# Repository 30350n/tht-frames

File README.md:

# THT-Frames

THT-Frames is a through hole version of [Mutable Instruments Frames](https://mutable-instruments.net/modules/frames/).
For the MCU a **128KB** STM32F103C8T6/STM32F103CBT6 "bluepill type" module is used.
**Warning! Most of the conventional boards floating around on ebay, aliexpress, etc. are 64KB. Those won't work with the provided firmware.**
I'd recommend picking one up from robotdyn ([website](https://robotdyn.com/)/[aliexpress](https://robotdyn.aliexpress.com/store/1950989)), these are the ones I use and they work without any problems.
You can also pickup a matching APM32 board if you want for a little cheaper. I've tested them and they also seem to work fine.

It also uses a different dac than the original, because it isn't available as a DIP package.

## Panels

Be sure to check out my [printable-instruments](https://github.com/30350n/printable-instruments) repository, which contains pcb panels for several Mutable Instuments modules including Frames.
That being said, any third-party panels should also fit with these boards.

## How to use

### Quickstart

To get started quickly, you can just download the gerbers for both pcbs and the compiled software `.hex` file from the [Releases](https://github.com/30350n/tht-frames/releases) section.

### Hardware

If you want to export the gerbers yourself or modify them, just clone the repository and open the hardware files with KiCad.

### Software

This project requires slightly modified software, because it uses two 2-channel DACs instead of the single 4-channel DAC the original uses.

If you want to build the software yourself, clone the [mutable-dev-environment](https://github.com/pichenettes/mutable-dev-environment) repository and follow the provided instructions to set it up.
After that, copy the patch from this repository (`software/tht-frames.patch`) to `mutable-dev-environment/eurorack-modules` and also `cd` to that directory.
Finally apply the patch via `git apply tht-frames.patch` and build the firmware as usual.

## Credits
- **[Mutable Instruments](https://github.com/pichenettes/eurorack)** provided the original hardware design files and software which this projects builds upon.
- **[SoundForce - Braids Through-hole](http://sound-force.nl/?page_id=3179)** gave me the idea for this project.

## License
- Hardware: cc-by-sa-3.0
- Software: MIT

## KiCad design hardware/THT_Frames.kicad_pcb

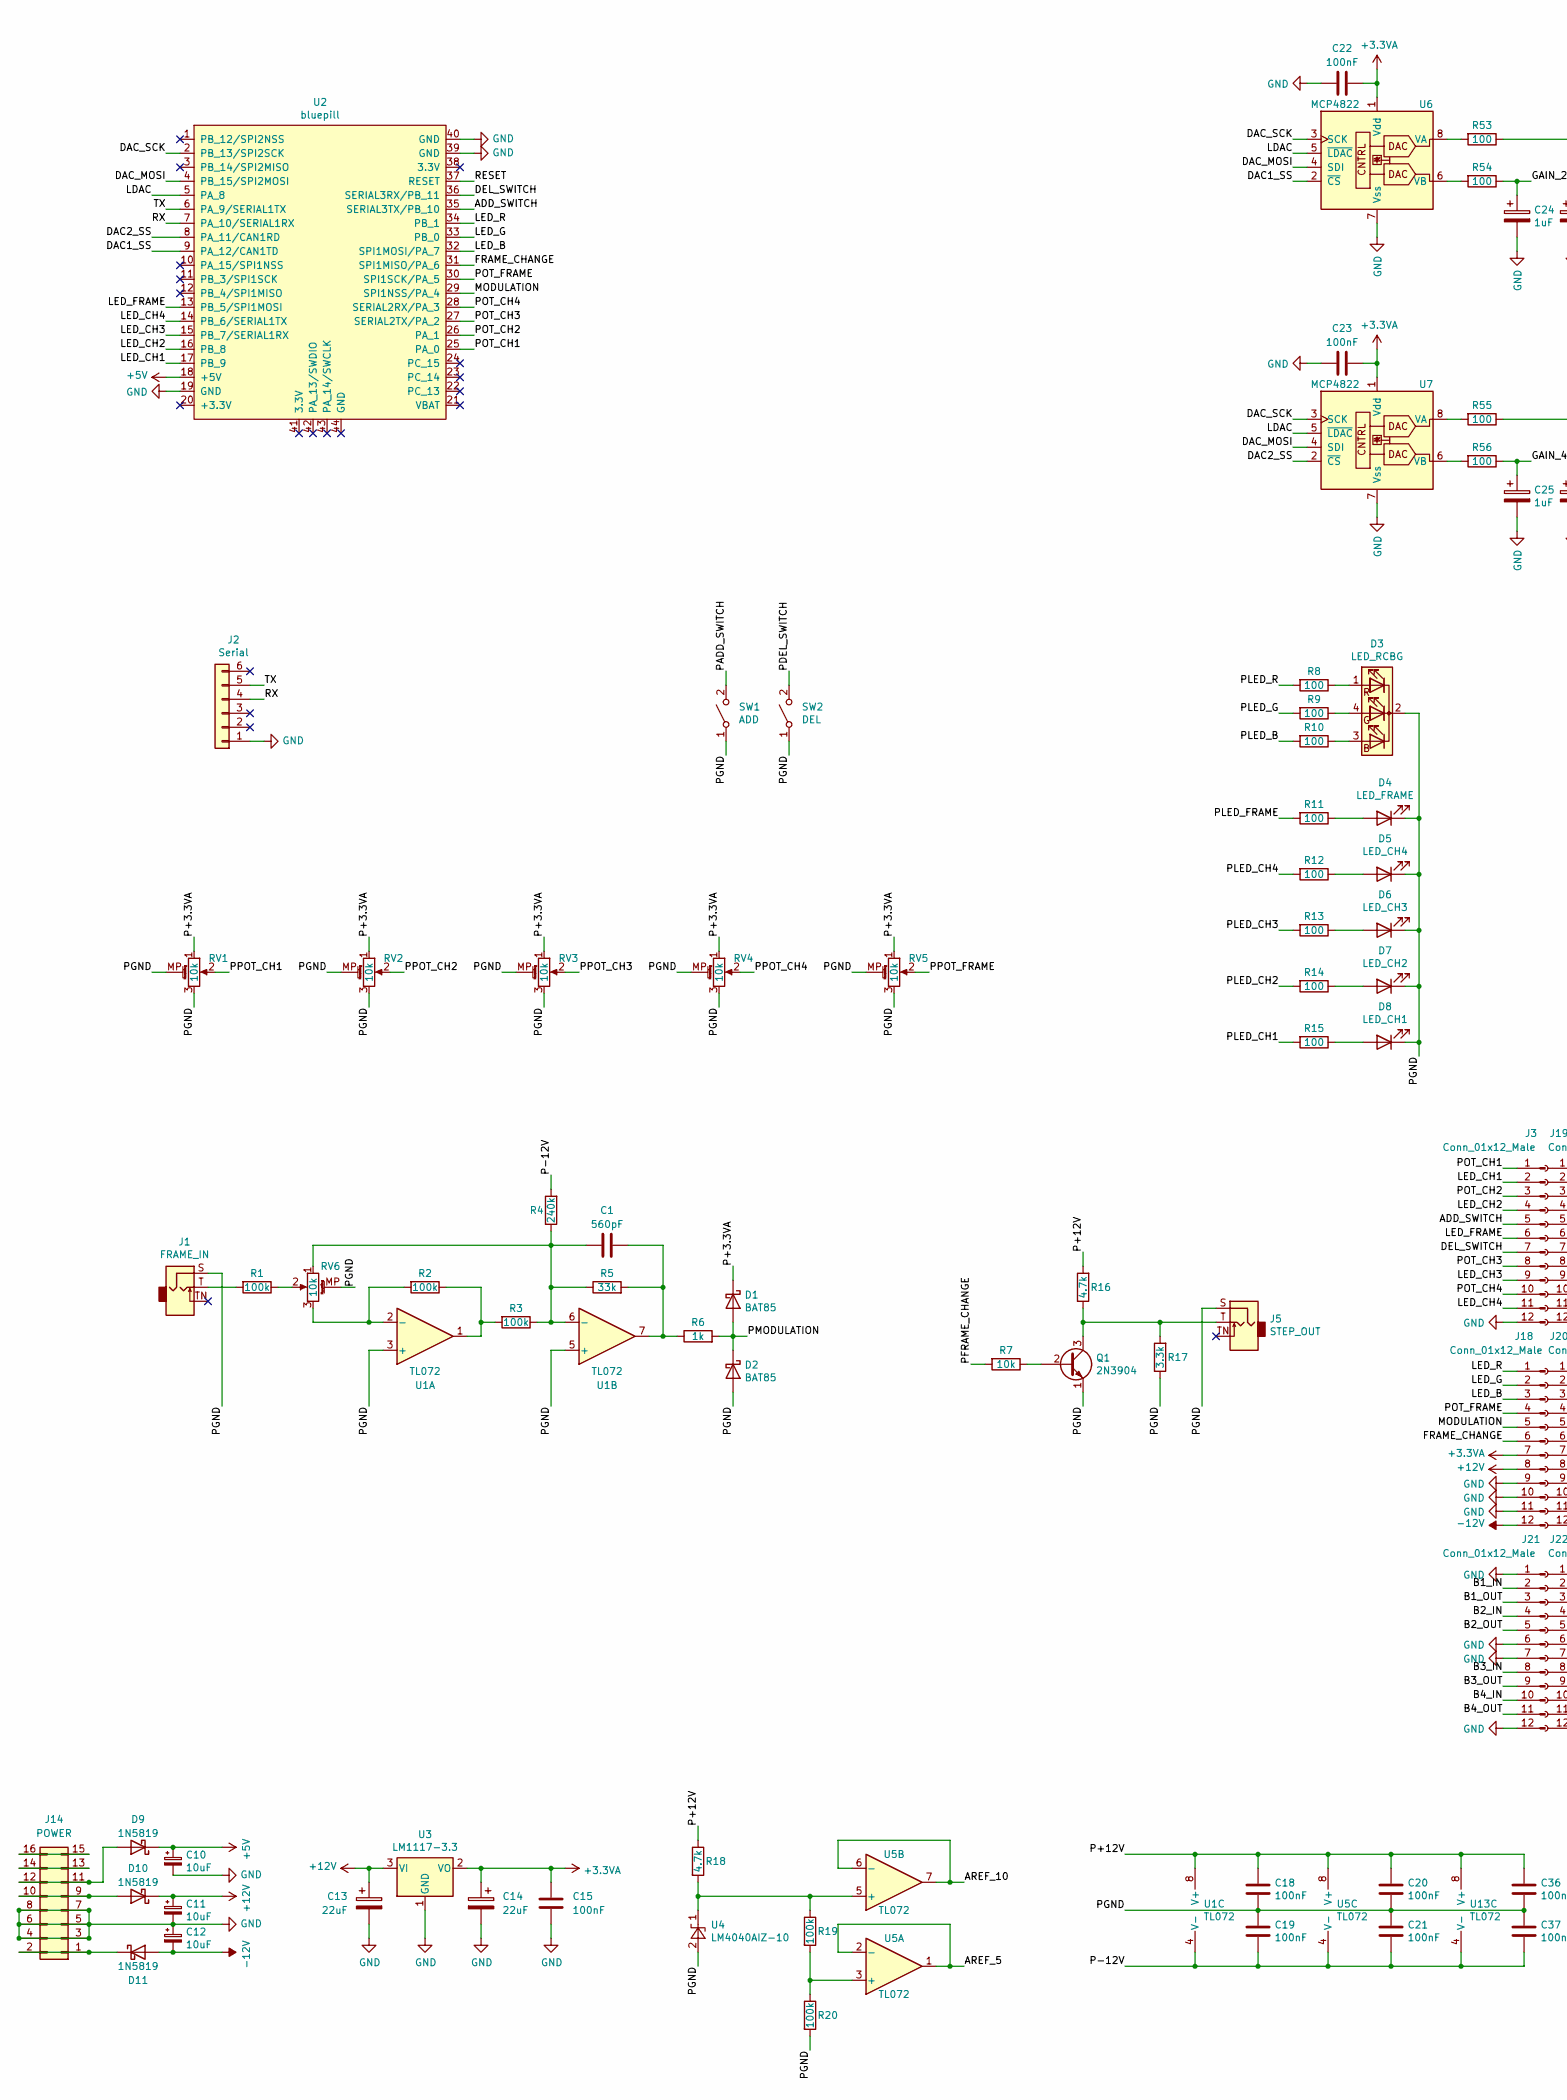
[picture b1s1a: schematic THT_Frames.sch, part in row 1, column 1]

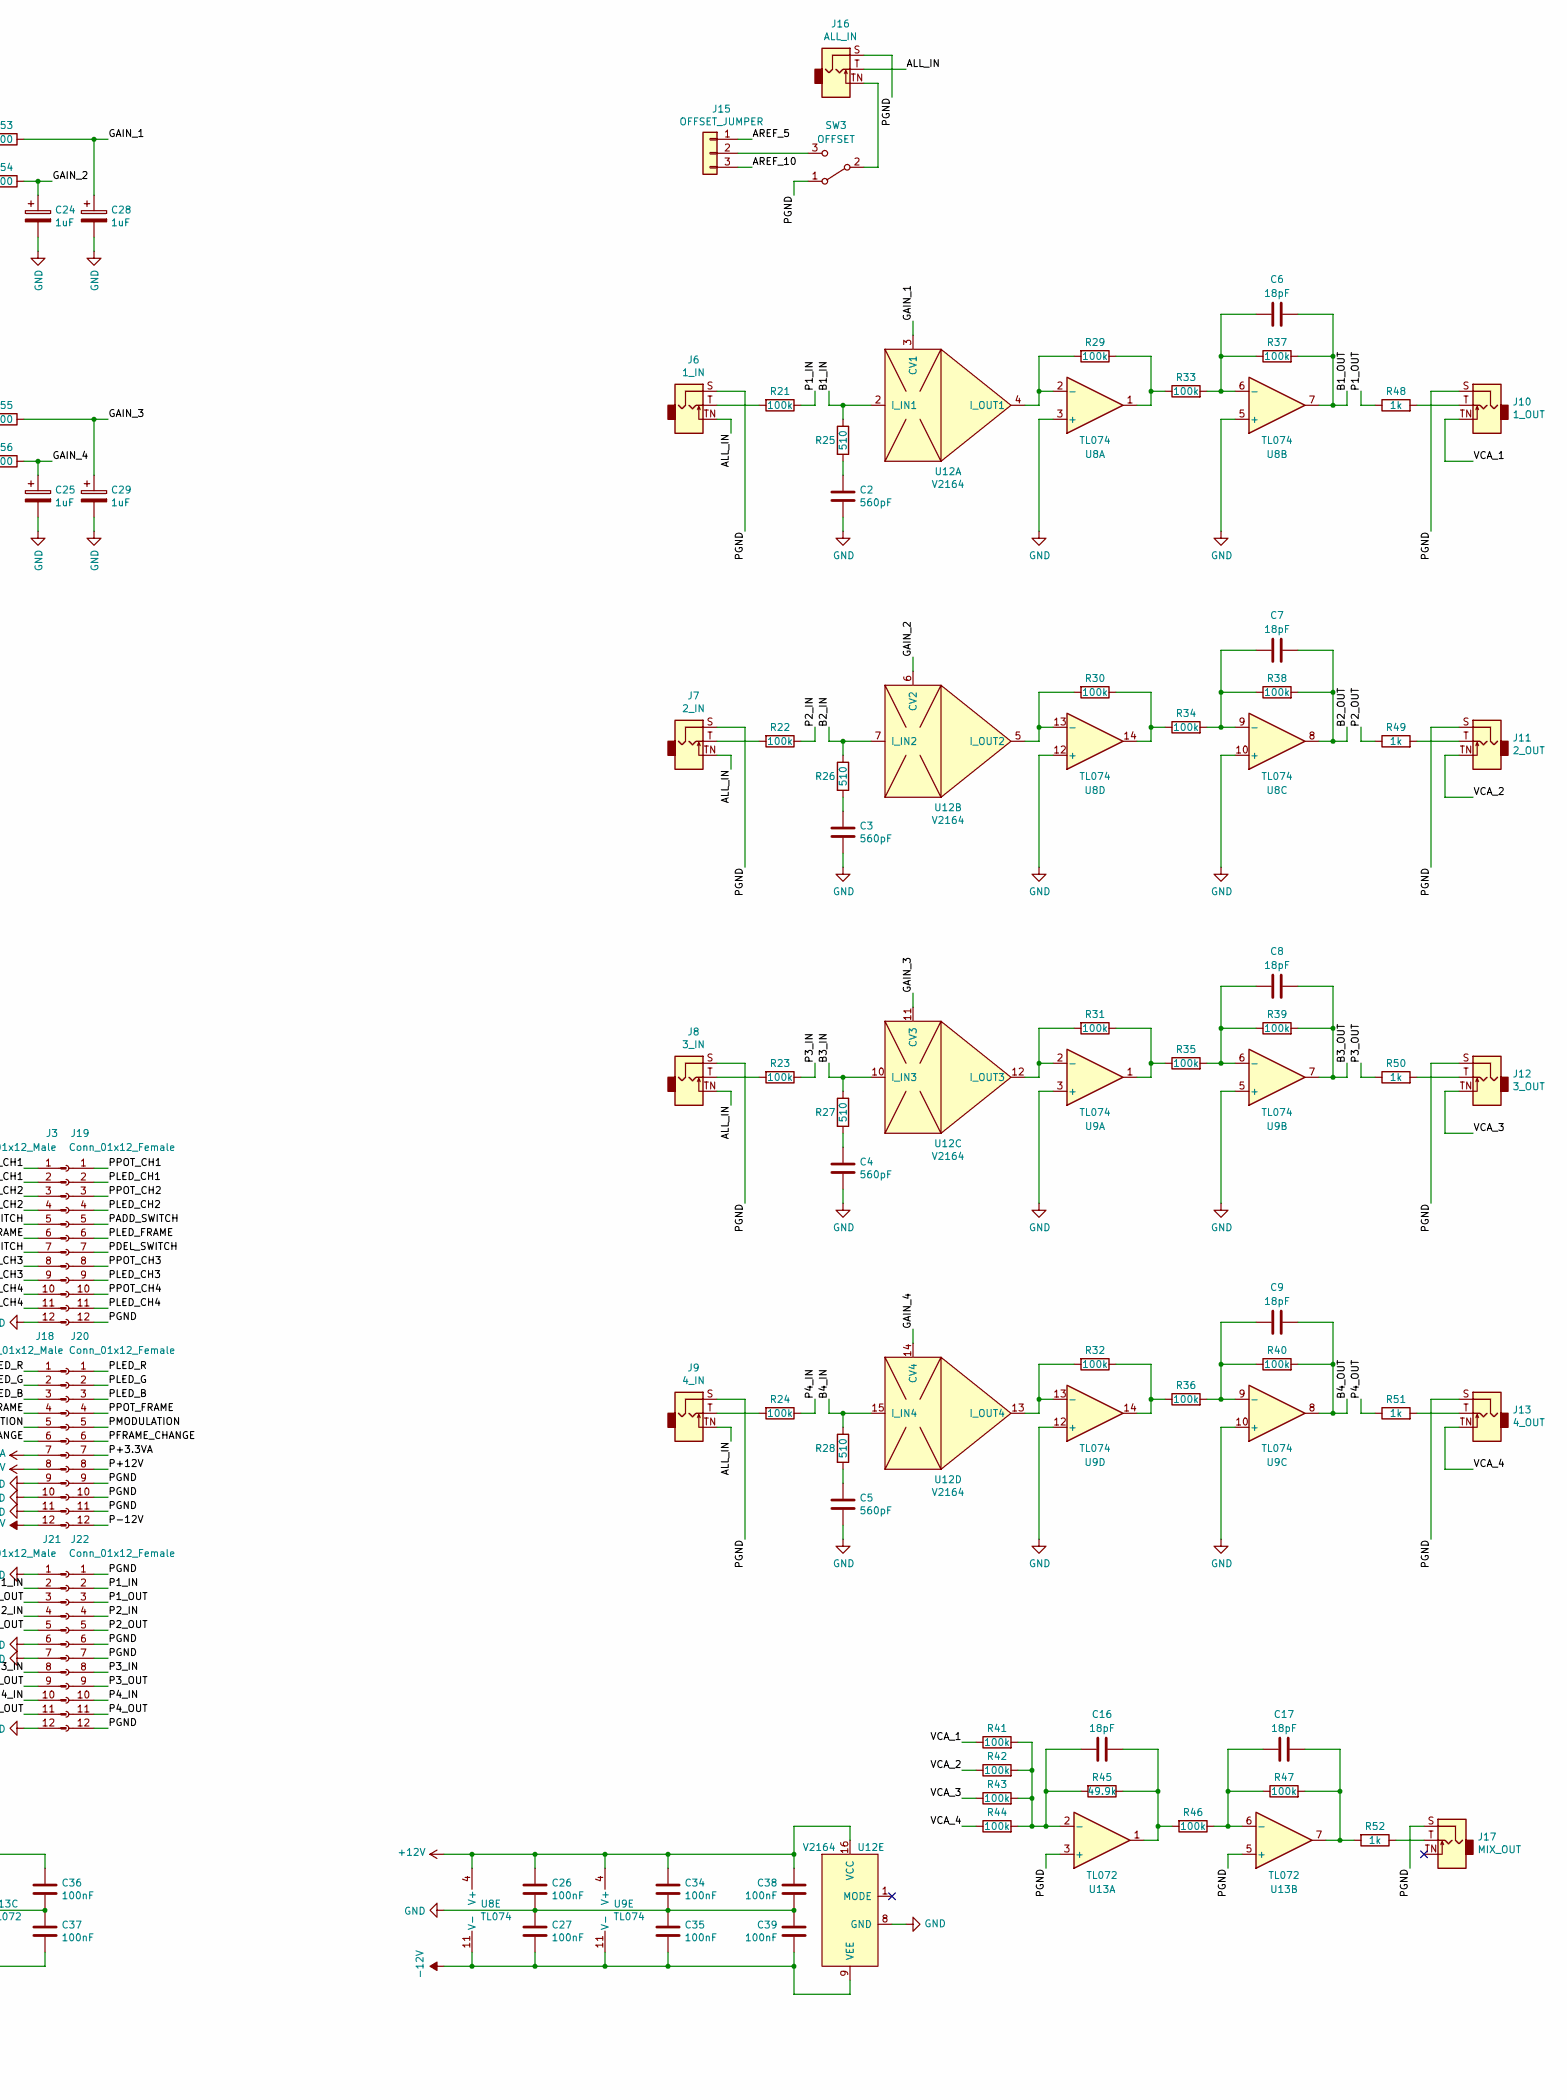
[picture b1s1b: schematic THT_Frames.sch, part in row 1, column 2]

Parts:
C1, C2, C3, C4, C5: 560pF; C_Disc_D5.0mm_W2.5mm_P5.00mm_silk
C6, C7, C8, C9, C16, C17: 18pF; C_Disc_D5.0mm_W2.5mm_P5.00mm_silk
C10, C11, C12: 10uF; CP_Radial_D5.0mm_P2.00mm_silk
C13, C14: 22uF; CP_Radial_D5.0mm_P2.00mm_silk
C15, C18, C19, C20, C21, C22, C23, C26, C27, C34, C35, C36, C37, C38, C39: 100nF; C_Disc_D5.0mm_W2.5mm_P5.00mm_silk
C24, C25, C28, C29: 1uF; C_Disc_D7.5mm_W5.0mm_P5.00mm_silk
D1, D2: BAT85; D_DO-41_SOD81_P7.62mm_Horizontal_silk
D3: LED_RCBG; LED_D5.0mm-4_RGB
D4: LED_FRAME; LED_D5.0mm
D5: LED_CH4; LED_D3.0mm
D6: LED_CH3; LED_D3.0mm
D7: LED_CH2; LED_D3.0mm
D8: LED_CH1; LED_D3.0mm
D9, D10, D11: 1N5819; D_DO-41_SOD81_P10.16mm_Horizontal_silk
J1: FRAME_IN; Jack_3.5mm_QingPu_WQP-PJ398SM_Vertical_CircularHoles_better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
J2: Serial; PinHeader_1x06_P2.54mm_Vertical
J3, J18, J21: Conn_01x12_Male; PinHeader_1x12_P2.54mm_Vertical
J5: STEP_OUT; Jack_3.5mm_QingPu_WQP-PJ398SM_Vertical_CircularHoles_better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
J6: 1_IN; Jack_3.5mm_QingPu_WQP-PJ398SM_Vertical_CircularHoles_better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
J7: 2_IN; Jack_3.5mm_QingPu_WQP-PJ398SM_Vertical_CircularHoles_better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
J8: 3_IN; Jack_3.5mm_QingPu_WQP-PJ398SM_Vertical_CircularHoles_better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
J9: 4_IN; Jack_3.5mm_QingPu_WQP-PJ398SM_Vertical_CircularHoles_better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
J10: 1_OUT; Jack_3.5mm_QingPu_WQP-PJ398SM_Vertical_CircularHoles_better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
J11: 2_OUT; Jack_3.5mm_QingPu_WQP-PJ398SM_Vertical_CircularHoles_better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
J12: 3_OUT; Jack_3.5mm_QingPu_WQP-PJ398SM_Vertical_CircularHoles_better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
J13: 4_OUT; Jack_3.5mm_QingPu_WQP-PJ398SM_Vertical_CircularHoles_better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
J14: POWER; IDC-Header_2x08_P2.54mm_Vertical_eurorack
J15: OFFSET_JUMPER; PinHeader_1x03_P2.54mm_Vertical
J16: ALL_IN; Jack_3.5mm_QingPu_WQP-PJ398SM_Vertical_CircularHoles_better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
J17: MIX_OUT; Jack_3.5mm_QingPu_WQP-PJ398SM_Vertical_CircularHoles_better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
J19, J20, J22: Conn_01x12_Female; PinSocket_1x12_P2.54mm_Vertical
Q1: 2N3904; TO-92_Inline_Wide_silk
R1, R2, R3, R19, R20, R21, R22, R23, R24, R29, R30, R31, R32, R33, R34, R35, R36, R37, R38, R39, R40, R41, R42, R43, R44, R46, R47: 100k; R_Axial_DIN0207_L6.3mm_D2.5mm_P7.62mm_Horizontal_silk
R4: 240k; R_Axial_DIN0207_L6.3mm_D2.5mm_P7.62mm_Horizontal_silk
R5: 33k; R_Axial_DIN0207_L6.3mm_D2.5mm_P7.62mm_Horizontal_silk
R6, R48, R49, R50, R51, R52: 1k; R_Axial_DIN0207_L6.3mm_D2.5mm_P7.62mm_Horizontal_silk
R7: 10k; R_Axial_DIN0207_L6.3mm_D2.5mm_P7.62mm_Horizontal_silk
R8, R9, R10, R11, R12, R13, R14, R15, R53, R54, R55, R56: 100; R_Axial_DIN0207_L6.3mm_D2.5mm_P7.62mm_Horizontal_silk
R16, R18: 4.7k; R_Axial_DIN0207_L6.3mm_D2.5mm_P7.62mm_Horizontal_silk
R17: 3.3k; R_Axial_DIN0207_L6.3mm_D2.5mm_P7.62mm_Horizontal_silk
R25, R26, R27, R28: 510; R_Axial_DIN0207_L6.3mm_D2.5mm_P7.62mm_Horizontal_silk
R45: 49.9k; R_Axial_DIN0207_L6.3mm_D2.5mm_P7.62mm_Horizontal_silk
RV1, RV2, RV3, RV4, RV5, RV6: 10k; Potentiometer_Alps_RK09K_Single_Vertical_better_origin
SW1: ADD; Push_E-Switch_KS01Q01_silk_better_origin
SW2: DEL; Push_E-Switch_KS01Q01_silk_better_origin
SW3: OFFSET; sw_spdt_slide_CS12ANW03
U1, U5, U13: TL072; DIP-8_W7.62mm_Socket_LongPads_silk
U2: bluepill
U3: LM1117-3.3; TO-220-3_Horizontal_TabDown_silk
U4: LM4040AIZ-10; TO-92_Inline_Wide_silk
U6, U7: MCP4822; DIP-8_W7.62mm_Socket_LongPads_silk
U8, U9: TL074; DIP-14_W7.62mm_Socket_LongPads_silk
U12: V2164; DIP-16_W7.62mm_Socket_LongPads_silk

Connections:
+3.3VA: C14.1, C15.1, C22.1, C23.1, J18.7, U3.2 (VO), U6.1 (Vdd), U7.1 (Vdd)
+5V: C10.1, D9.1 (K), U2.18 (+5V)
+12V: C11.1, C13.1, C26.1, C34.1, C38.1, D10.1 (K), J18.8, U3.3 (VI), U8.4 (V+), U9.4 (V+), U12.16 (VCC)
-12V: C12.2, C27.2, C35.2, C39.2, D11.2 (A), J18.12, U8.11 (V-), U9.11 (V-), U12.9 (VEE)
/ADD_SWITCH: J3.5, U2.35 (SERIAL3TX/PB_10)
/ALL_IN: J6.TN, J7.TN, J8.TN, J9.TN, J16.T
/AREF_5: J15.1, U5.1, U5.2 (-)
/AREF_10: J15.3, U5.6 (-), U5.7
/B1_IN: J21.2, R25.1, U12.2 (I_IN1)
/B1_OUT: C6.1, J21.3, R37.2, U8.7
/B2_IN: J21.4, R26.1, U12.7 (I_IN2)
/B2_OUT: C7.1, J21.5, R38.2, U8.8
/B3_IN: J21.8, R27.1, U12.10 (I_IN3)
/B3_OUT: C8.1, J21.9, R39.2, U9.7
/B4_IN: J21.10, R28.1, U12.15 (I_IN4)
/B4_OUT: C9.1, J21.11, R40.2, U9.8
/DAC1_SS: U2.9 (PA_12/CAN1TD), U6.2 (~CS)
/DAC2_SS: U2.8 (PA_11/CAN1RD), U7.2 (~CS)
/DAC_MOSI: U2.4 (PB_15/SPI2MOSI), U6.4 (SDI), U7.4 (SDI)
/DAC_SCK: U2.2 (PB_13/SPI2SCK), U6.3 (SCK), U7.3 (SCK)
/DEL_SWITCH: J3.7, U2.36 (SERIAL3RX/PB_11)
/FRAME_CHANGE: J18.6, U2.31 (SPI1MISO/PA_6)
/GAIN_1: C28.1, R53.1, U12.3 (CV1)
/GAIN_2: C24.1, R54.1, U12.6 (CV2)
/GAIN_3: C29.1, R55.1, U12.11 (CV3)
/GAIN_4: C25.1, R56.1, U12.14 (CV4)
/LDAC: U2.5 (PA_8), U6.5 (~LDAC), U7.5 (~LDAC)
/LED_B: J18.3, U2.32 (SPI1MOSI/PA_7)
/LED_CH1: J3.2, U2.17 (PB_9)
/LED_CH2: J3.4, U2.16 (PB_8)
/LED_CH3: J3.9, U2.15 (PB_7/SERIAL1RX)
/LED_CH4: J3.11, U2.14 (PB_6/SERIAL1TX)
/LED_FRAME: J3.6, U2.13 (PB_5/SPI1MOSI)
/LED_G: J18.2, U2.33 (PB_0)
/LED_R: J18.1, U2.34 (PB_1)
/MODULATION: J18.5, U2.29 (SPI1NSS/PA_4)
/P1_IN: J22.2, R21.1
/P1_OUT: J22.3, R48.1
/P2_IN: J22.4, R22.1
/P2_OUT: J22.5, R49.1
/P3_IN: J22.8, R23.1
/P3_OUT: J22.9, R50.1
/P4_IN: J22.10, R24.1
/P4_OUT: J22.11, R51.1
/P+3.3VA: D1.1 (K), J20.7, RV1.1, RV2.1, RV3.1, RV4.1, RV5.1
/P+12V: C18.1, C20.1, C36.1, J20.8, R16.2, R18.1, U1.8 (V+), U5.8 (V+), U13.8 (V+)
/P-12V: C19.2, C21.2, C37.2, J20.12, R4.2, U1.4 (V-), U5.4 (V-), U13.4 (V-)
/PADD_SWITCH: J19.5, SW1.2 (B)
/PDEL_SWITCH: J19.7, SW2.2 (B)
/PFRAME_CHANGE: J20.6, R7.2
/PGND: C18.2, C19.1, C20.2, C21.1, C36.2, C37.1, D2.2 (A), D3.2 (K), D4.1 (K), D5.1 (K), D6.1 (K), D7.1 (K), D8.1 (K), J1.S, J5.S, J6.S, J7.S, J8.S, J9.S, J10.S, J11.S, J12.S, J13.S, J16.S, J17.S, J19.12, J20.9, J20.10, J20.11, J22.1, J22.6, J22.7, J22.12, Q1.1 (E), R17.1, R20.2, RV1.3, RV1.MP (MountPin), RV2.3, RV2.MP (MountPin), RV3.3, RV3.MP (MountPin), RV4.3, RV4.MP (MountPin), RV5.3, RV5.MP (MountPin), RV6.MP (MountPin), SW1.1 (A), SW2.1 (A), SW3.1 (A), U1.3 (+), U1.5 (+), U4.2 (A), U13.3 (+), U13.5 (+)
/PLED_B: J20.3, R10.2
/PLED_CH1: J19.2, R15.2
/PLED_CH2: J19.4, R14.2
/PLED_CH3: J19.9, R13.2
/PLED_CH4: J19.11, R12.2
/PLED_FRAME: J19.6, R11.2
/PLED_G: J20.2, R9.2
/PLED_R: J20.1, R8.2
/PMODULATION: D1.2 (A), D2.1 (K), J20.5, R6.2
/POT_CH1: J3.1, U2.25 (PA_0)
/POT_CH2: J3.3, U2.26 (PA_1)
/POT_CH3: J3.8, U2.27 (SERIAL2TX/PA_2)
/POT_CH4: J3.10, U2.28 (SERIAL2RX/PA_3)
/POT_FRAME: J18.4, U2.30 (SPI1SCK/PA_5)
/PPOT_CH1: J19.1, RV1.2
/PPOT_CH2: J19.3, RV2.2
/PPOT_CH3: J19.8, RV3.2
/PPOT_CH4: J19.10, RV4.2
/PPOT_FRAME: J20.4, RV5.2
/RESET: U2.37 (RESET)
/RX: J2.4, U2.7 (PA_10/SERIAL1RX)
/TX: J2.5, U2.6 (PA_9/SERIAL1TX)
/VCA_1: J10.TN, R41.1
/VCA_2: J11.TN, R42.1
/VCA_3: J12.TN, R43.1
/VCA_4: J13.TN, R44.1
GND: C2.2, C3.2, C4.2, C5.2, C10.2, C11.2, C12.1, C13.2, C14.2, C15.2, C22.2, C23.2, C24.2, C25.2, C26.2, C27.1, C28.2, C29.2, C34.2, C35.1, C38.2, C39.1, J2.1, J3.12, J14.3, J14.4, J14.5, J14.6, J14.7, J14.8, J18.9, J18.10, J18.11, J21.1, J21.6, J21.7, J21.12, U2.19 (GND), U2.39 (GND), U2.40 (GND), U3.1 (GND), U6.7 (Vss), U7.7 (Vss), U8.3 (+), U8.5 (+), U8.10 (+), U8.12 (+), U9.3 (+), U9.5 (+), U9.10 (+), U9.12 (+), U12.8 (GND)
unnamed: C1.1, R5.2, R6.1, U1.7
unnamed: C1.2, R3.1, R4.1, R5.1, RV6.1, U1.6 (-)
unnamed: C2.1, R25.2
unnamed: C3.1, R26.2
unnamed: C4.1, R27.2
unnamed: C5.1, R28.2
unnamed: C6.2, R33.2, R37.1, U8.6 (-)
unnamed: C7.2, R34.2, R38.1, U8.9 (-)
unnamed: C8.2, R35.2, R39.1, U9.6 (-)
unnamed: C9.2, R36.2, R40.1, U9.9 (-)
unnamed: C16.1, R45.1, R46.2, U13.1
unnamed: C16.2, R41.2, R42.2, R43.2, R44.2, R45.2, U13.2 (-)
unnamed: C17.1, R47.2, R52.2, U13.7
unnamed: C17.2, R46.1, R47.1, U13.6 (-)
unnamed: D3.1 (RA), R8.1
unnamed: D3.3 (BA), R10.1
unnamed: D3.4 (GA), R9.1
unnamed: D4.2 (A), R11.1
unnamed: D5.2 (A), R12.1
unnamed: D6.2 (A), R13.1
unnamed: D7.2 (A), R14.1
unnamed: D8.2 (A), R15.1
unnamed: D9.2 (A), J14.11, J14.12
unnamed: D10.2 (A), J14.9, J14.10
unnamed: D11.1 (K), J14.1, J14.2
unnamed: J1.T, R1.2
unnamed: J5.T, Q1.3 (C), R16.1, R17.2
unnamed: J6.T, R21.2
unnamed: J7.T, R22.2
unnamed: J8.T, R23.2
unnamed: J9.T, R24.2
unnamed: J10.T, R48.2
unnamed: J11.T, R49.2
unnamed: J12.T, R50.2
unnamed: J13.T, R51.2
unnamed: J14.13, J14.14
unnamed: J14.15, J14.16
unnamed: J15.2, SW3.3 (C)
unnamed: J16.TN, SW3.2 (B)
unnamed: J17.T, R52.1
unnamed: Q1.2 (B), R7.1
unnamed: R1.1, RV6.2
unnamed: R2.1, R3.2, U1.1
unnamed: R2.2, RV6.3, U1.2 (-)
unnamed: R18.2, R19.1, U4.1 (K), U5.5 (+)
unnamed: R19.2, R20.1, U5.3 (+)
unnamed: R29.1, R33.1, U8.1
unnamed: R29.2, U8.2 (-), U12.4 (I_OUT1)
unnamed: R30.1, R34.1, U8.14
unnamed: R30.2, U8.13 (-), U12.5 (I_OUT2)
unnamed: R31.1, R35.1, U9.1
unnamed: R31.2, U9.2 (-), U12.12 (I_OUT3)
unnamed: R32.1, R36.1, U9.14
unnamed: R32.2, U9.13 (-), U12.13 (I_OUT4)
unnamed: R53.2, U6.8 (VA)
unnamed: R54.2, U6.6 (VB)
unnamed: R55.2, U7.8 (VA)
unnamed: R56.2, U7.6 (VB)

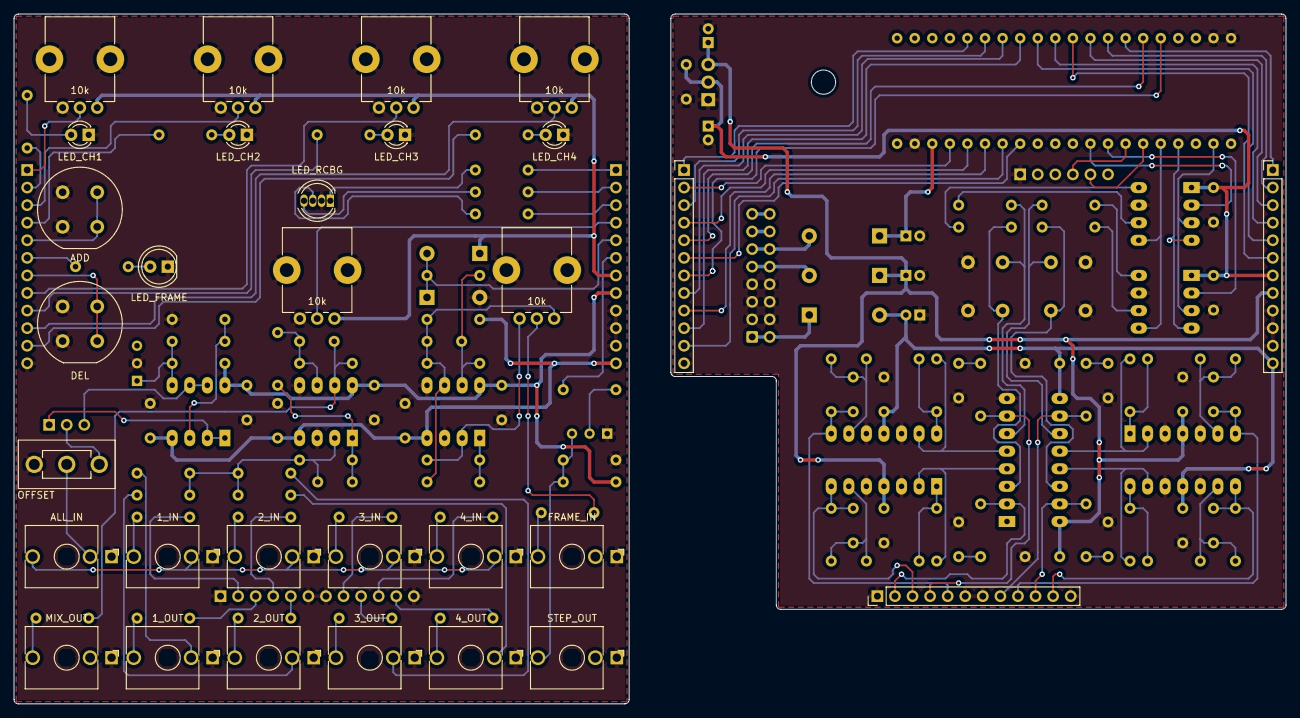
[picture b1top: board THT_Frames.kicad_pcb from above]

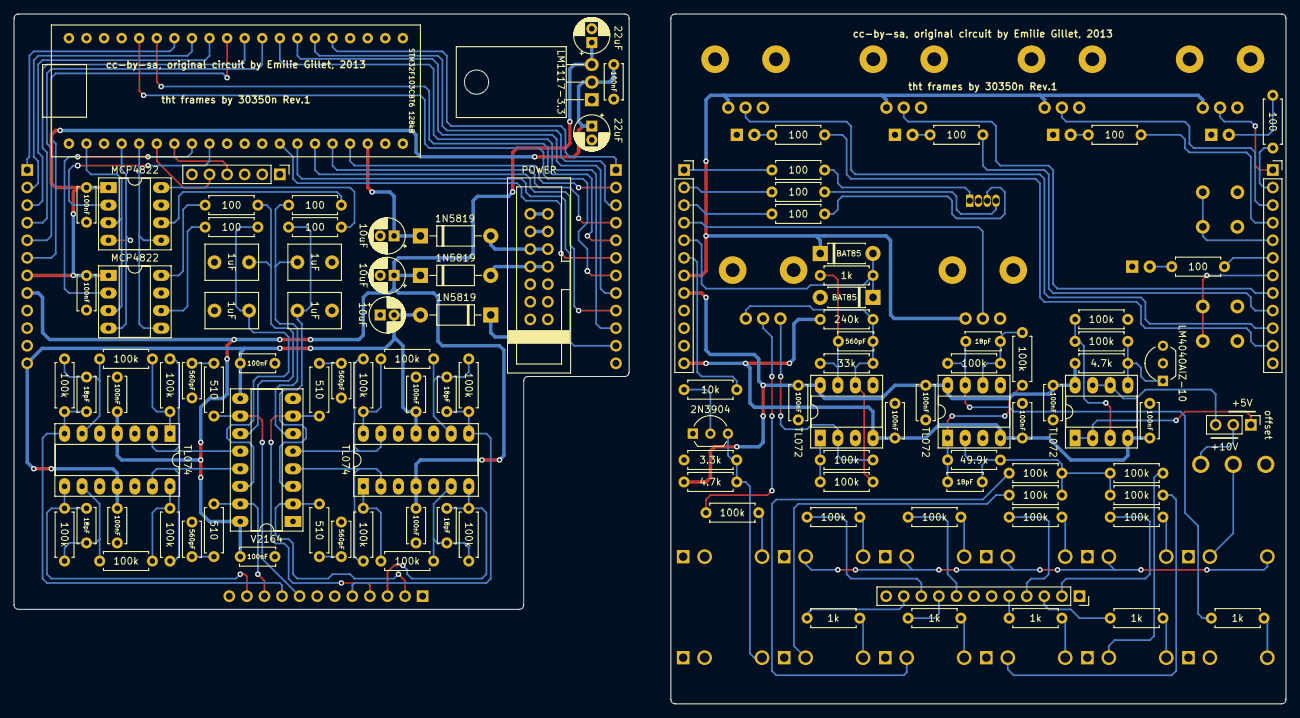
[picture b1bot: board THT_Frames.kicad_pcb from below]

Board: 2 copper layers, 183.8 x 99.7 mm, 144 parts (114 on the bottom side), 135 nets.

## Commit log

2020-10-26 Add development hardware files
2020-10-26 Fix swapped leds on channels 3/4
2020-10-26 Use easy to solder to-92 footprint, bigger footprints for 1uF caps
2020-10-26 Add silkscreen markings to offset jumper
2020-10-26 Fix accidentally inverted internal offset voltages
2020-10-30 Remove cache/rescue files from repo
2020-10-30 Add cache/rescue files to gitignore
2020-11-25 Add guide to README, Add software
2020-11-25 Bump revision number on main pcb
2022-01-31 Add note about panels to readme, Add ibom
2022-01-31 Add schematic cache

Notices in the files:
hardware/THT_Frames.kicad_pcb:
cc-by-sa, original circuit by Emilie Gillet, 2013
